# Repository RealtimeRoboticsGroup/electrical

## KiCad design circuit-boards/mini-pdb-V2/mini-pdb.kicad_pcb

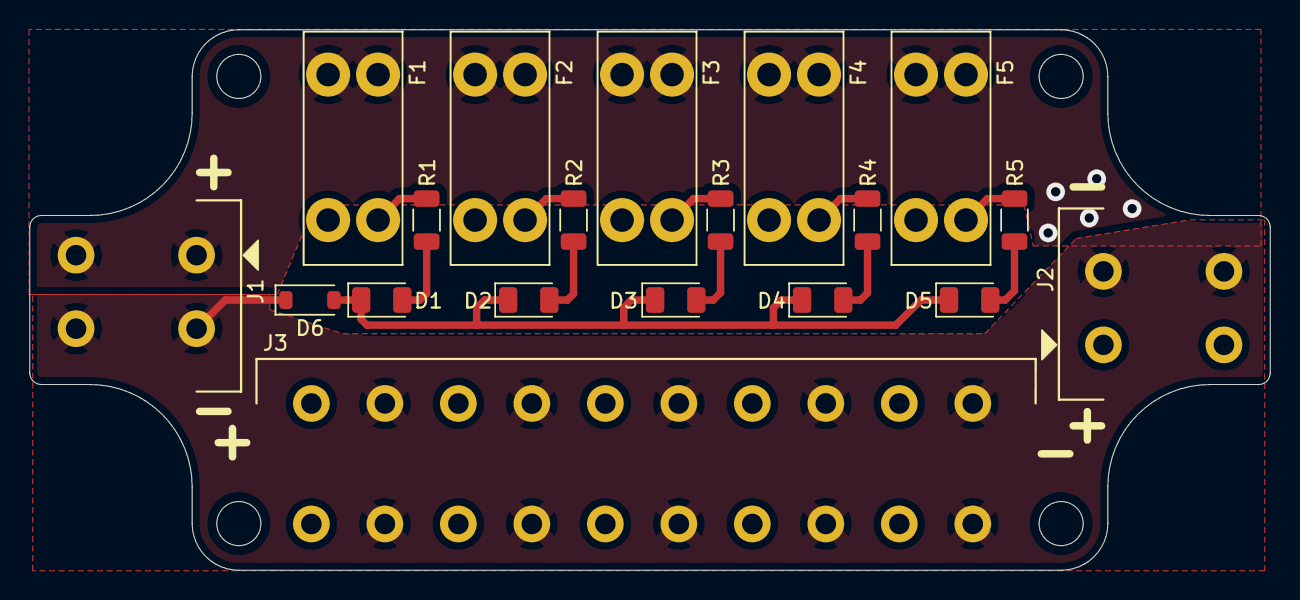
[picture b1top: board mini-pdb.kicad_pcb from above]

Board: 2 copper layers, 84.4 x 36.8 mm, 23 parts (0 on the bottom side), 13 nets.

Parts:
D1, D2, D3, D4, D5: QTLP651C4TR; LED_1206_3216Metric
D6: MMSD914T3G; D_SOD-123
F1, F2, F3, F4, F5: ATM Fuse Holder; Keystone-3568
H1, H2, H3, H4: MountingHole; MountingHole_3.2mm_M3
J1, J2: 2604-1102; Wago-2604-1102
J3: 2604-1110; Wago-2604-1110
R1, R2, R3, R4, R5: 1k-1%-1206; R_1206_3216Metric

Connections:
/F1_OUT: F1.2, J3.1, R1.2
/F2_OUT: F2.2, J3.3, R2.2
/F3_OUT: F3.2, J3.5, R3.2
/F4_OUT: F4.2, J3.7, R4.2
/F5_OUT: F5.2, J3.9, R5.2
/VBAT+: F1.1, F2.1, F3.1, F4.1, F5.1, J1.1, J2.1
/VBAT-: D6.1 (K), J1.2, J2.2, J3.2, J3.4, J3.6, J3.8, J3.10
unnamed: D1.2 (A), R1.1
unnamed: D1.1 (K), D2.1 (K), D3.1 (K), D4.1 (K), D5.1 (K), D6.2 (A)
unnamed: D2.2 (A), R2.1
unnamed: D3.2 (A), R3.1
unnamed: D4.2 (A), R4.1
unnamed: D5.2 (A), R5.1

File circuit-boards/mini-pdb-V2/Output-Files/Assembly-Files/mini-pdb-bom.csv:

"Item","QUANTITY","Reference","Value","MFG","MFG P/N","DIST","DIST P/N"
"1","1","D6","MMSD914T3G","onsemi","MMSD914T3G","Digikey","MMSD914T3GOSCT-ND"
"2","5","D1-D5","QTLP651C4TR","Everlight Electronics Co Ltd","QTLP651C4TR","DIGIKEY","QTLP651C4TR"
"3","5","F1-F5","ATM Fuse Holder","Keystone","3568","Digikey","36-3568-ND"
"4","5","FUSE1-FUSE5","7.5A","Littelfuse Inc.","029707.5L","DIGIKEY","F4269-ND"
"5","1","J3","2604-1110","WAGO","2604-1110","DIGIKEY","2946-2604-1110-ND"
"6","2","J1,J2","2604-1102","WAGO","2604-1102","DIGIKEY","2946-2604-1102-ND"
"7","5","R1-R5","1k-1%-1206","Stackpole Electronics Inc","RMCF1206FT1K00","DIGIKEY","RMCF1206FT1K00"

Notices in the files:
parts and their libraries:
Copyright 2016 Accelerated Designs. All rights reserved.
